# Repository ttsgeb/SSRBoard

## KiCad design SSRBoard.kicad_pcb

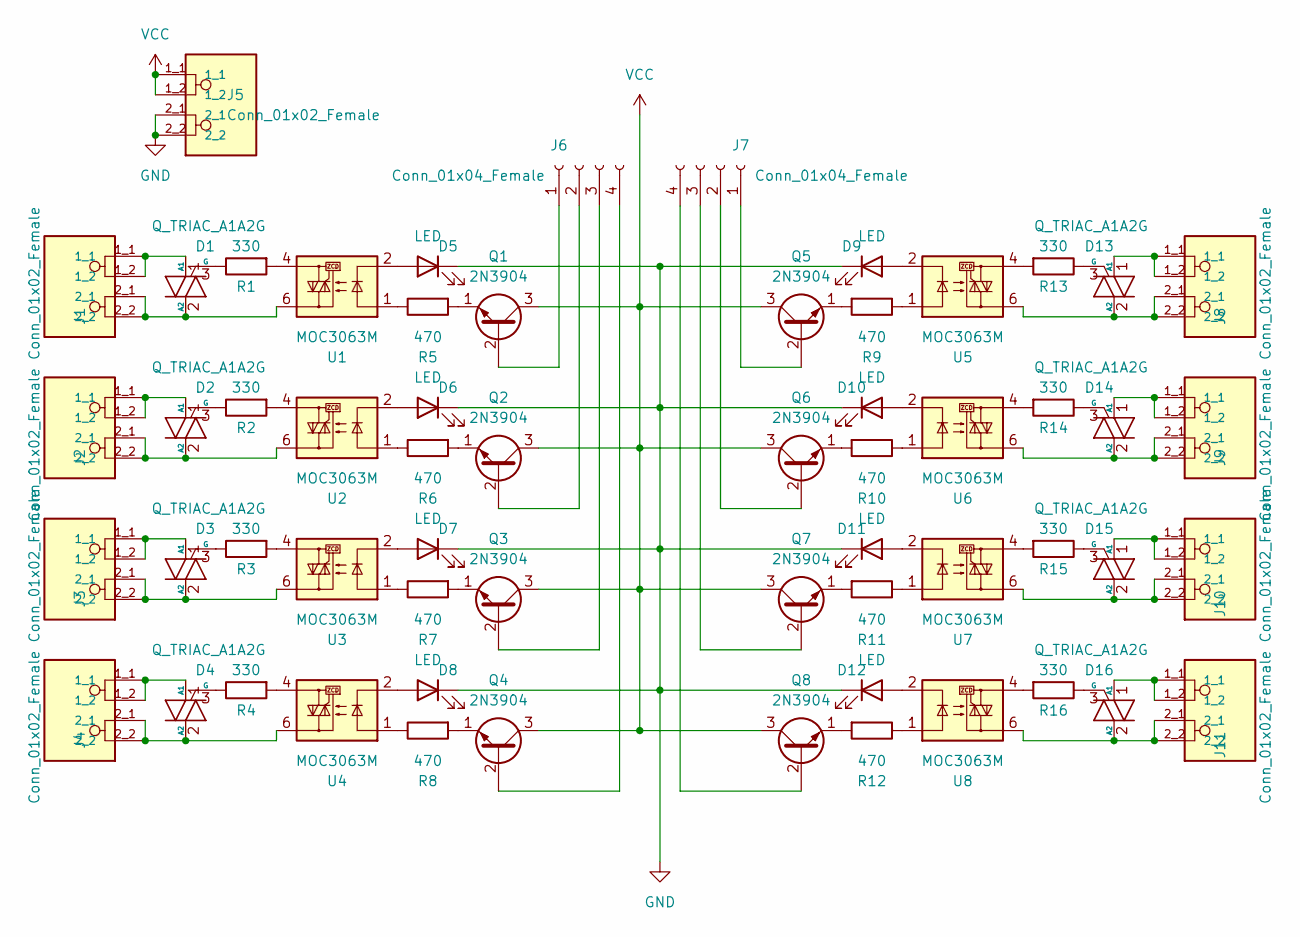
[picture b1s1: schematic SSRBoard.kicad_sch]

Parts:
D1, D2, D3, D4, D13, D14, D15, D16: Q_TRIAC_A1A2G; TO-220-3_Vertical
D5, D6, D7, D8, D9, D10, D11, D12: LED; LED_D3.0mm
J1, J2, J3, J4, J5, J8, J9, J10, J11: Conn_01x02_Female; PHOENIX_1990973; PARTREV 27.09.2023
J6, J7: Conn_01x04_Female; PinHeader_1x04_P2.54mm_Vertical
Q1, Q2, Q3, Q4, Q5, Q6, Q7, Q8: 2N3904; TO-92_Inline
R1, R2, R3, R4, R13, R14, R15, R16: 330; R_Axial_DIN0207_L6.3mm_D2.5mm_P7.62mm_Horizontal
R5, R6, R7, R8, R9, R10, R11, R12: 470; R_Axial_DIN0207_L6.3mm_D2.5mm_P7.62mm_Horizontal
U1, U2, U3, U4, U5, U6, U7, U8: MOC3063M; DIP-6_W7.62mm

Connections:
GND: D5.1 (K), D6.1 (K), D7.1 (K), D8.1 (K), D9.1 (K), D10.1 (K), D11.1 (K), D12.1 (K), J5.2_1, J5.2_2
unnamed: D1.1 (A1), J1.1_1, J1.1_2
unnamed: D1.3 (G), R1.1
unnamed: D2.1 (A1), J2.1_1, J2.1_2
unnamed: D2.2 (A2), J2.2_1, J2.2_2, U2.6
unnamed: D2.3 (G), R2.1
unnamed: D3.1 (A1), J3.1_1, J3.1_2
unnamed: D3.2 (A2), J3.2_1, J3.2_2, U3.6
unnamed: D3.3 (G), R3.1
unnamed: D4.1 (A1), J4.1_1, J4.1_2
unnamed: D4.2 (A2), J4.2_1, J4.2_2, U4.6
unnamed: D4.3 (G), R4.1
unnamed: D6.2 (A), U2.2
unnamed: D7.2 (A), U3.2
unnamed: D8.2 (A), U4.2
unnamed: D9.2 (A), U5.2
unnamed: D10.2 (A), U6.2
unnamed: D11.2 (A), U7.2
unnamed: D12.2 (A), U8.2
unnamed: D13.1 (A1), J8.1_1, J8.1_2
unnamed: D13.2 (A2), J8.2_1, J8.2_2, U5.6
unnamed: D13.3 (G), R13.1
unnamed: D14.1 (A1), J9.1_1, J9.1_2
unnamed: D14.2 (A2), J9.2_1, J9.2_2, U6.6
unnamed: D14.3 (G), R14.1
unnamed: D15.1 (A1), J10.1_1, J10.1_2
unnamed: D15.2 (A2), J10.2_1, J10.2_2, U7.6
unnamed: D15.3 (G), R15.1
unnamed: D16.1 (A1), J11.1_1, J11.1_2
unnamed: D16.2 (A2), J11.2_1, J11.2_2, U8.6
unnamed: D16.3 (G), R16.1
unnamed: D1.2 (A2), J1.2_1, J1.2_2, U1.6
unnamed: J6.1, Q1.2 (B)
unnamed: J6.2, Q2.2 (B)
unnamed: J6.3, Q3.2 (B)
unnamed: J6.4, Q4.2 (B)
unnamed: J7.1, Q5.2 (B)
unnamed: J7.2, Q6.2 (B)
unnamed: J7.3, Q7.2 (B)
unnamed: J7.4, Q8.2 (B)
unnamed: Q2.1 (E), R6.2
unnamed: Q3.1 (E), R7.2
unnamed: Q4.1 (E), R8.2
unnamed: Q5.1 (E), R9.2
unnamed: Q6.1 (E), R10.2
unnamed: Q7.1 (E), R11.2
unnamed: Q8.1 (E), R12.2
unnamed: R1.2, U1.4
unnamed: R2.2, U2.4
unnamed: R3.2, U3.4
unnamed: R4.2, U4.4
unnamed: R5.1, U1.1
unnamed: Q1.1 (E), R5.2
unnamed: R6.1, U2.1
unnamed: R7.1, U3.1
unnamed: R8.1, U4.1
unnamed: R9.1, U5.1
unnamed: R10.1, U6.1
unnamed: R11.1, U7.1
unnamed: R12.1, U8.1
unnamed: R13.2, U5.4
unnamed: R14.2, U6.4
unnamed: R15.2, U7.4
unnamed: R16.2, U8.4
unnamed: D5.2 (A), U1.2
VCC: J5.1_1, J5.1_2, Q1.3 (C), Q2.3 (C), Q3.3 (C), Q4.3 (C), Q5.3 (C), Q6.3 (C), Q7.3 (C), Q8.3 (C)

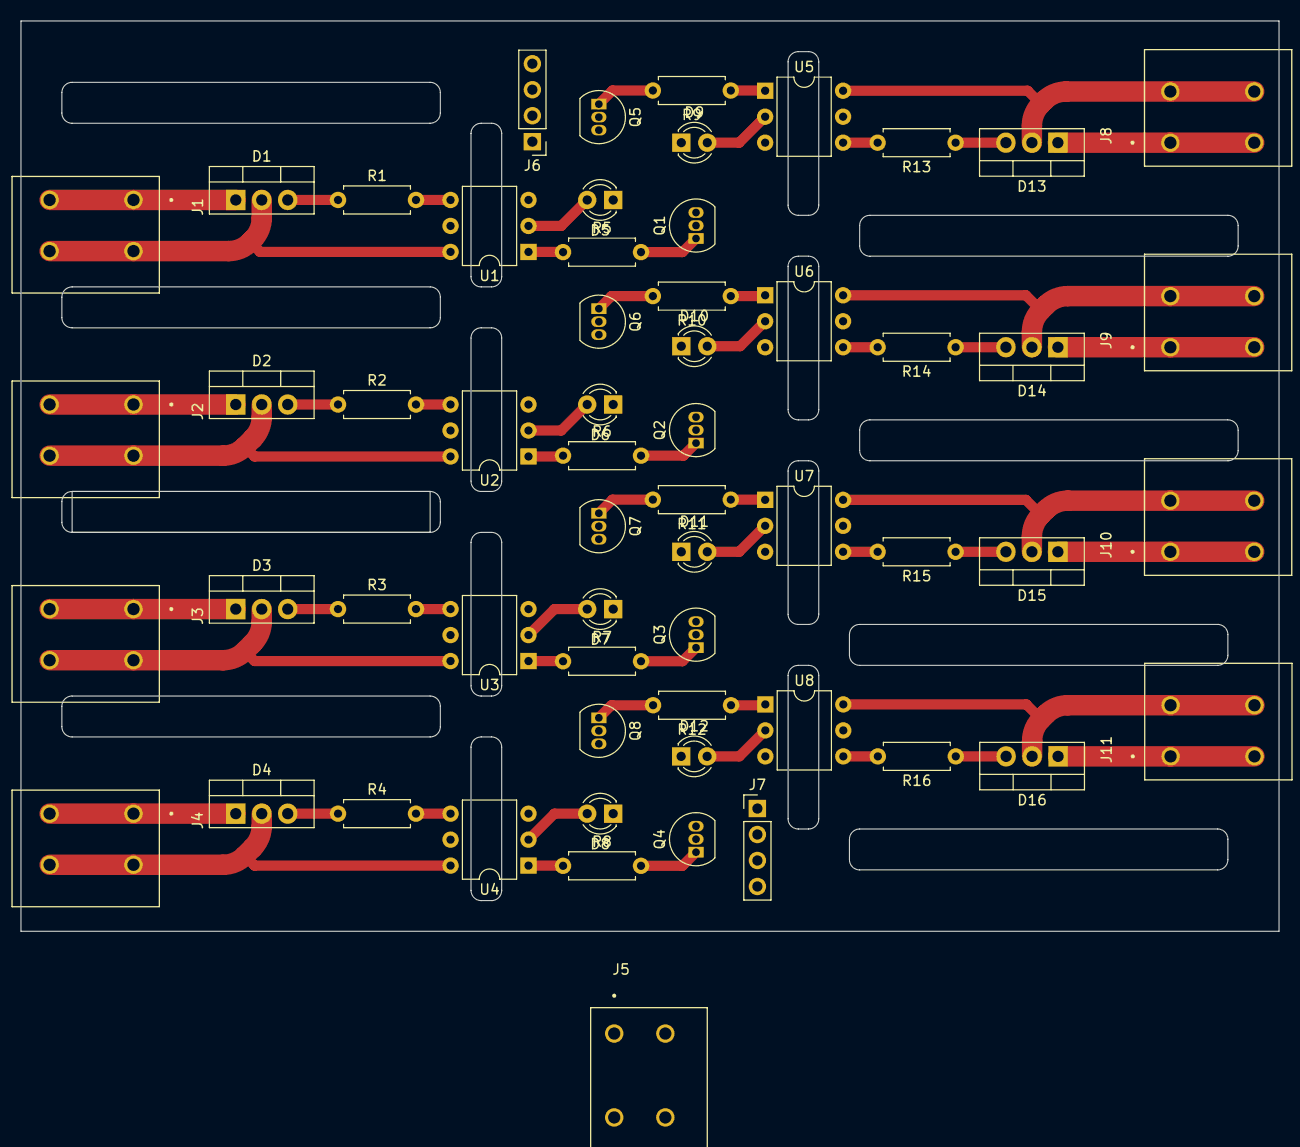
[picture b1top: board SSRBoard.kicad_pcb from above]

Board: 2 copper layers, 123.0 x 89.0 mm, 59 parts (0 on the bottom side), 66 nets.
